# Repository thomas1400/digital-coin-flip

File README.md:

# digital-coin-flip
A hardware project, my first experience with circuit design and PCB layout. 

My "digital coin flip" is a circuit that simulates flipping a coin and randomly lights up a "heads" or "tails" LED. When you press the "flip" button, it connects a fast oscillator to the clock input of a JK flip-flop with J and K held high, which rapidly flips the JK flip-flop's output, Q, between high and low. When you release the button, the flip-flop's state is held, with a roughly equal chance of ending up in either the high or low state (given the rapid clock speed and unpredictable length of a button-press). Then, Q and !Q are fed into the gates of two transistors, which switch power to the "heads" and "tails" LEDs, respectively.

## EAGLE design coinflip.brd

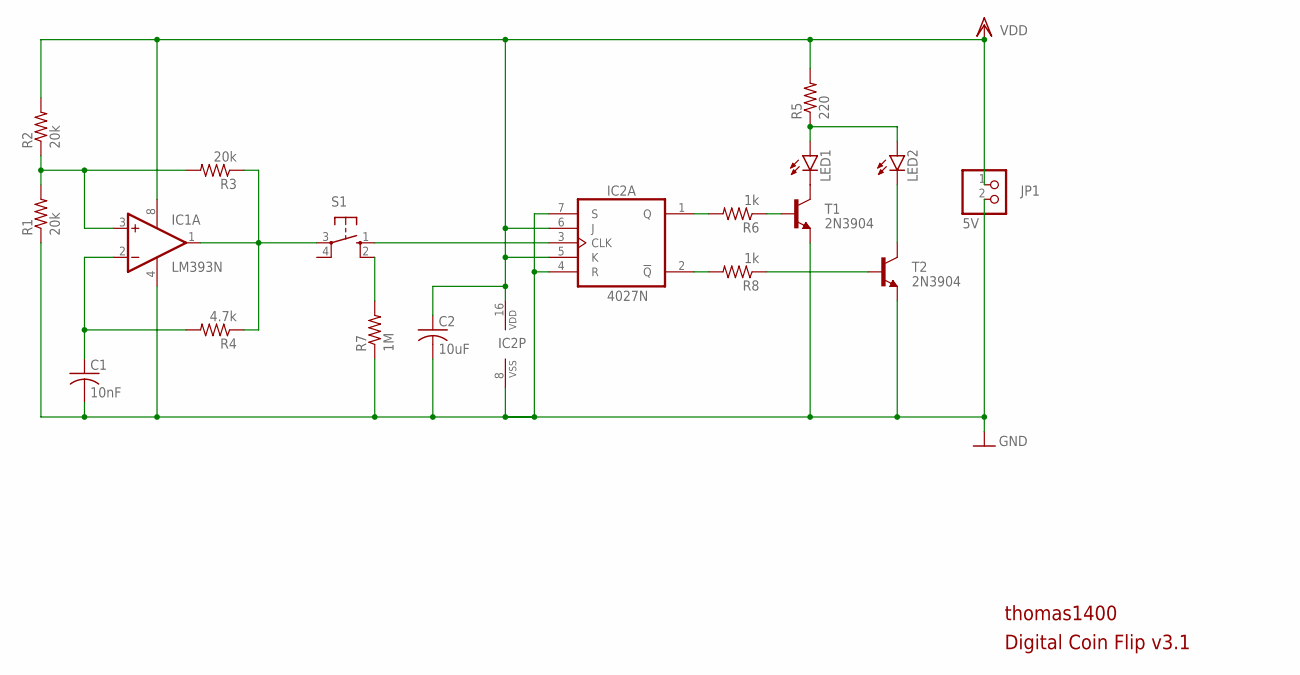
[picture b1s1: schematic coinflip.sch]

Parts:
C1: 10nF; C050-024X044
C2: 10uF; C050-024X044
IC1: LM393N; DIL08
IC2: 4027N; DIL16
JP1: 5V; 1X02
LED1, LED2: LED3MM
R1, R2, R3: 20k; 0207/10
R4: 4.7k; 0207/10
R5: 220; 0207/10
R6, R8: 1k; 0207/10
R7: 1M; 0207/10
S1: 10-XX; B3F-10XX
T1, T2: 2N3904; TO92

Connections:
GND: C1.2, C2.2, IC1.4 (V-), IC2.4 (R), IC2.7 (S), IC2.8 (VSS), JP1.2, R1.1, R7.1, T1.3 (E), T2.3 (E)
unnamed: IC1.1 (OUT), R3.1, R4.1, S1.3
unnamed: IC1.3 (+IN), R1.2, R2.1, R3.2
unnamed: C1.1, IC1.2 (-IN), R4.2
unnamed: IC2.1 (Q), R6.2
unnamed: R7.2, S1.2 (S1)
unnamed: R6.1, T1.2 (B)
unnamed: IC2.2 (!Q), R8.2
unnamed: R8.1, T2.2 (B)
unnamed: LED1.K (C), T1.1 (C)
unnamed: LED1.A, LED2.A, R5.1
unnamed: IC2.3 (CLK), S1.1 (S)
unnamed: LED2.K (C), T2.1 (C)
VDD: C2.1, IC1.8 (V+), IC2.5 (K), IC2.6 (J), IC2.16 (VDD), JP1.1, R2.2, R5.2

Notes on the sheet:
Digital Coin Flip v3.1
thomas1400

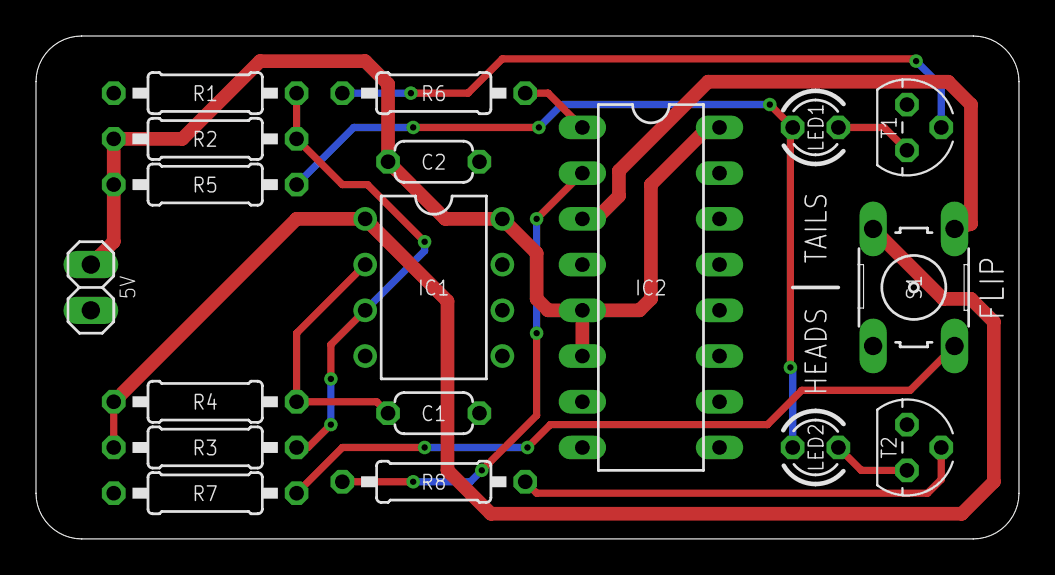
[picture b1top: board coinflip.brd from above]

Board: 2 copper layers, 54.6 x 27.9 mm, 18 parts (0 on the bottom side), 14 nets.

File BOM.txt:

Partlist exported from C:/Users/thoma/Documents/EAGLE/projects/Digital Coin Flip/coinflip.sch at 11/28/2020 5:09 PM

Part Value  Device          Package      Description                
C1   10nF   C-US050-024X044 C050-024X044 CAPACITOR, American symbol 
C2   10uF   C-US050-024X044 C050-024X044 CAPACITOR, American symbol 
IC1  LM393N LM393N          DIL08        COMPARATOR                 
IC2  4027N  4027N           DIL16        Dual JK FLIP FLOP          
JP1  5V     PINHD-1X2       1X02         PIN HEADER                 
LED1        LED3MM          LED3MM       LED                        
LED2        LED3MM          LED3MM       LED                        
R1   20k    R-US_0207/10    0207/10      RESISTOR, American symbol  
R2   20k    R-US_0207/10    0207/10      RESISTOR, American symbol  
R3   20k    R-US_0207/10    0207/10      RESISTOR, American symbol  
R4   4.7k   R-US_0207/10    0207/10      RESISTOR, American symbol  
R5   220    R-US_0207/10    0207/10      RESISTOR, American symbol  
R6   1k     R-US_0207/10    0207/10      RESISTOR, American symbol  
R7   1M     R-US_0207/10    0207/10      RESISTOR, American symbol  
R8   1k     R-US_0207/10    0207/10      RESISTOR, American symbol  
S1          10-XX           B3F-10XX     OMRON SWITCH               
T1   2N3904 2N3904          TO92         NPN TRANSISTOR             
T2   2N3904 2N3904          TO92         NPN TRANSISTOR

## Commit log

2020-11-23 Version 1.0 commit
2020-11-23 Version 2.0 commit
2020-11-24 Added V2 images
2020-11-28 Updated to v3.0: redesigned oscillator, new board layout
2020-11-28 Version 3.1, added BOM and adjusted routing and silkscreen
2020-11-29 Aligned bottom silkscreen text
